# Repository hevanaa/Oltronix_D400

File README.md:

# Oltronix D400-007D Regulator Board (KiCad redesign)

This repository contains a redesigned regulator board for the Oltronix D400-007D 400 V DC power supply.

The goal of this redesign is improved safety margins, better component availability, and improved PCB high-voltage layout compared to the original design.

---

## Project structure

- `/project/`  
  KiCad PCB and schematic files

- `/production/`  
  Gerber files, drill files

- `/docs/`  
  Documentation, and reference material

- `/bom/`  
  Bill of Materials (CSV / spreadsheet format)

---

## Design overview

This board replaces the original regulator / error amplifier section of the power supply.

Key improvements include:
- Increased high-voltage clearance in critical areas
- Improved creepage distance at edge connector
- Use of modern, readily available components
- Slight circuit refinements for reliability (e.g. protection diode on driver stage)

---

## PCB design notes

### Edge connector safety improvement

The original design used a single-sided PCB edge connector layout, resulting in insufficient clearance between high-voltage pins (notably 220 V AC input and ~320–360 V DC rail).

This redesign uses a **double-sided alternating pad layout**, where connector contacts are split between top and bottom layers.

This achieves:
- Significantly increased creepage distance (>5 mm effective)
- Reduced risk of carbon tracking and flashover
- Improved robustness under contamination and aging

Pad geometry was also adjusted to better match connector cavity dimensions.

---

## Component labeling convention

This project follows the original Oltronix reference designators where possible.

- **T1, T2, T3** → Transistors  
- **D1, D2, D3** → Diodes  
- **Rxx** → Resistors (high-voltage / power-rated where specified)  
- **Cxx** → Capacitors  
- **P1** → Adjustment potentiometer / calibration trimmer  

When deviations from the original design exist, they are documented in the schematic notes.

---

## Manufacturing notes

- Standard 1.6 mm FR-4 PCB thickness assumed
- High-voltage areas require clean routing and no solder mask contamination in critical creepage zones
- Some resistors must withstand elevated voltage stress and should not be substituted with generic low-voltage types

---

## Adjustments

P1 must be adjusted during commissioning as described in the accompanying blog article:
https://baldpenguin.blogspot.com/2026/04/another-oltronix-power-supply-d400-007d.html

---

## External documentation

Detailed design rationale, repair notes, and BOM information are documented in accompanying articles:

- Part 1 (design analysis and failure modes):  
  https://baldpenguin.blogspot.com/2026/04/another-oltronix-power-supply-d400-007d.html

- Part 2 (repair implementation and BOM details):  
  https://baldpenguin.blogspot.com/2026/06/repairing-oltronix-d400-007d-part-2.html

Part 2 contains practical component substitutions and ordering examples.

---

## License

This repository contains a redesigned replacement for the regulator board used in the Oltronix D400-007D power supply.

The original device and schematic are the property of their respective rights holders and are not included under this license.

This project covers only the original work created in this repository, including the PCB layout, modified schematic, BOM, and documentation.

This project is licensed under the CERN-OHL-S v2 (Strongly Reciprocal).

See `LICENSE` file for details.

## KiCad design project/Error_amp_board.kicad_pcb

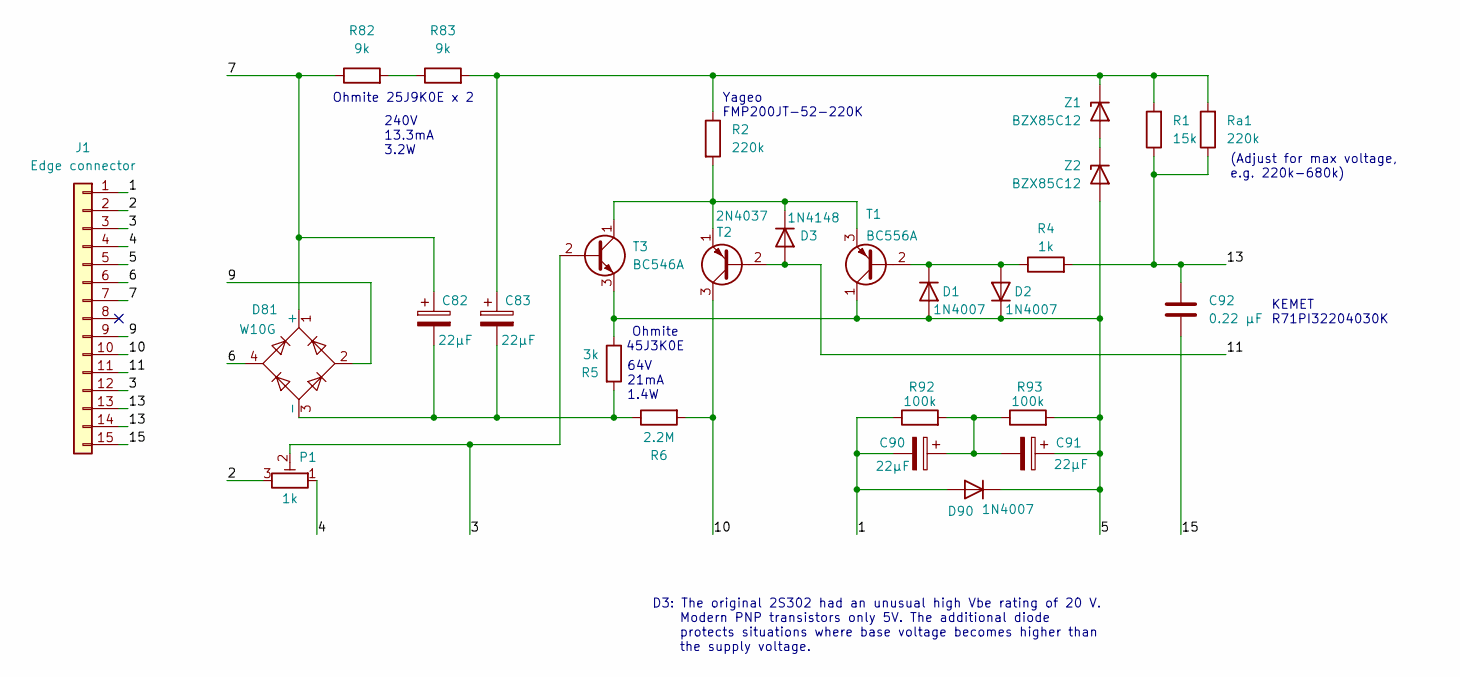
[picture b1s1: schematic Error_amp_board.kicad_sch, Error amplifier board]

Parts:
C82, C83: 22µF; CP_Radial_D16.0mm_P7.50mm
C90, C91: 22µF; CP_Radial_D10.0mm_P5.00mm
C92: 0.22 µF; C_Rect_L18.0mm_W8.0mm_P15.00mm_FKS3_FKP3
D1: 1N4007; D_DO-41_SOD81_P5.08mm_Vertical_AnodeUp
D2: 1N4007; D_DO-41_SOD81_P5.08mm_Vertical_CathodeUp
D3: 1N4148; D_DO-35_SOD27_P3.81mm_Vertical_CathodeUp
D81: W10G; Diode_Bridge_Round_D9.8mm
D90: 1N4007; D_DO-41_SOD81_P10.16mm_Horizontal
J1: Edge connector; Oltronix_HV_board_edge_connector_15
P1: 1k; Potentiometer_Piher_PT-10-V10_Vertical
R1: 15k; R_Axial_DIN0411_L9.9mm_D3.6mm_P5.08mm_Vertical
R2: 220k; R_Axial_DIN0411_L9.9mm_D3.6mm_P5.08mm_Vertical
R4: 1k; R_Axial_DIN0414_L11.9mm_D4.5mm_P5.08mm_Vertical
R5: 3k; R_Axial_Power_L25.0mm_W9.0mm_P7.62mm_Vertical
R6: 2.2M; R_Axial_DIN0411_L9.9mm_D3.6mm_P5.08mm_Vertical
R82, R83: 9k; R_Axial_Power_L25.4mm_W7mm_P27.94mm
R92, R93: 100k; R_Axial_DIN0516_L15.5mm_D5.0mm_P5.08mm_Vertical
Ra1: 220k; R_Axial_DIN0411_L9.9mm_D3.6mm_P5.08mm_Vertical
T1: BC556A; TO-92_Inline_Wide
T2: 2N4037; TO-39-3
T3: BC546A; TO-92_Inline_Wide
Z1, Z2: BZX85C12; D_DO-41_SOD81_P5.08mm_Vertical_AnodeUp

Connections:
/1: C90.2, D90.2 (A), J1.1, R92.1
/2: J1.2, P1.3
/3: J1.3, J1.12, P1.2, T3.2 (B)
/4: J1.4, P1.1
/5: C91.1, D1.2 (A), D2.1 (K), D90.1 (K), J1.5, R5.1, R93.2, T1.1 (C), T3.3 (E), Z2.2 (A)
/6: D81.4, J1.6
/7: C82.1, D81.1 (+), J1.7, R82.1
/9: D81.2, J1.9
/10: J1.10, R6.2, T2.3 (C)
/11: D3.2 (A), J1.11, T2.2 (B)
/13: C92.1, J1.13, J1.14, R1.1, R4.2, Ra1.1
/15: C92.2, J1.15
unnamed: C90.1, C91.2, R92.2, R93.1
unnamed: D1.1 (K), D2.2 (A), R4.1, T1.2 (B)
unnamed: D3.1 (K), R2.2, T1.3 (E), T2.1 (E), T3.1 (C)
unnamed: C82.2, C83.2, D81.3 (-), R5.2, R6.1
unnamed: R82.2, R83.1
unnamed: Z1.2 (A), Z2.1 (K)
unnamed: C83.1, R1.2, R2.1, R83.2, Ra1.2, Z1.1 (K)

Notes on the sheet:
KEMET R71PI32204030K
Ohmite 45J3K0E
D3: The original 2S302 had an unusual high Vbe rating of 20 V. Modern PNP transistors only 5V. The additional diode protects situations where base voltage becomes higher than the supply voltage.
Yageo FMP200JT-52-220K
240V 13.3mA 3.2W
64V 21mA 1.4W
Ohmite 25J9K0E x 2
(Adjust for max voltage, e.g. 220k-680k)

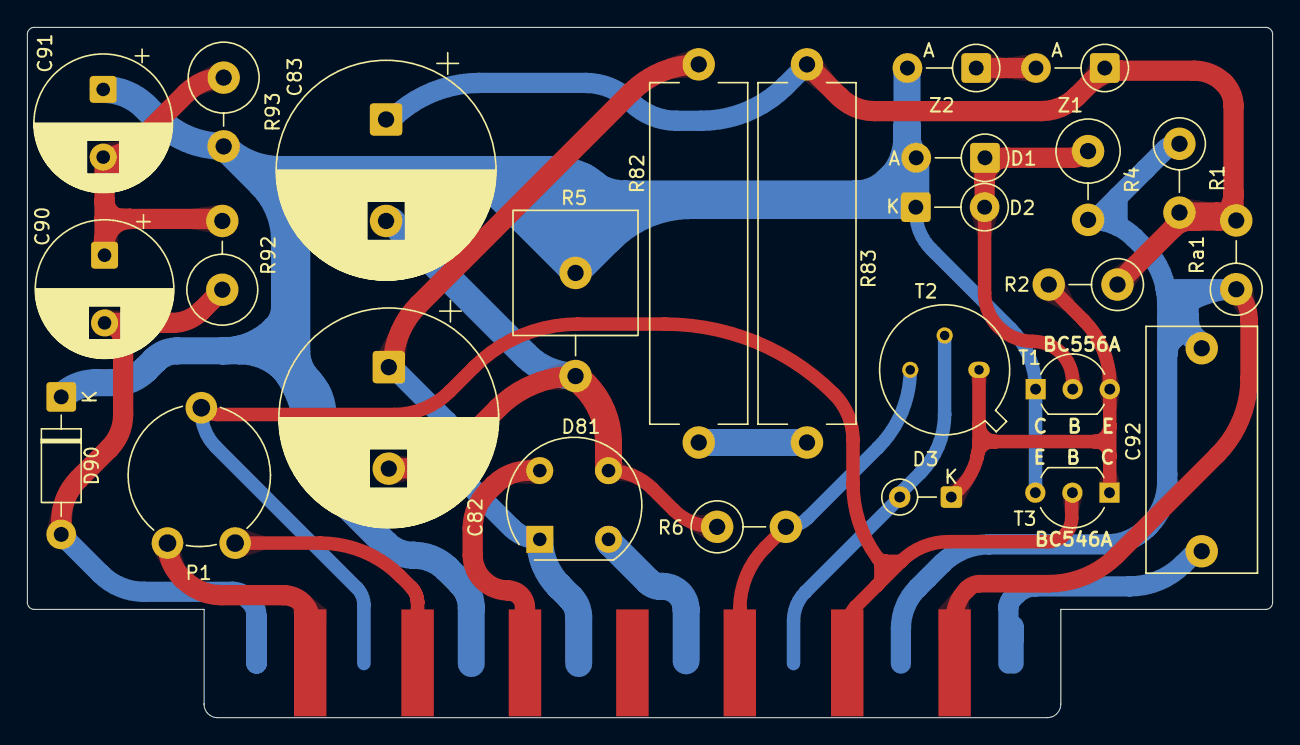
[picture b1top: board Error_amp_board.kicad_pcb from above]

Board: 2 copper layers, 92.0 x 51.0 mm, 27 parts (1 on the bottom side), 19 nets.

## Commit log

2026-06-27 added bom
2026-06-27 added board picture
